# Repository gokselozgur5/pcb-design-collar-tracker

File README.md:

# Collar Tracker

**A GNSS + cellular dog tracker, engineered across hardware, firmware and enclosure.**

A custom six-layer PCB, a persistent position-delivery pipeline and an adjustable collar mount.
Designed for factory assembly, with versioned sources and reproducible verification.

**Stage:** engineering prototype. PCB fabrication checks pass; assembly approval and physical validation remain open.

[Explore the CAD package](release/collar-tracker-3d-universal-mount-r01.zip) · [Current status](docs/STATUS.md) · [Verification](#verification) · [Start here](#inspect-and-reproduce)

## At a glance

| Hardware | Firmware & service | Mechanical design |
| --- | --- | --- |
| **40 × 32 mm**, six copper layers | **C / Zephyr / nRF Connect SDK** | **57.4 × 49.4 × 21 mm** rigid enclosure |
| nRF9151 · GNSS · LTE-M · nano-SIM | Persistent outbox · mTLS · watchdog recovery | Retained PCB and battery · gasketed lid |
| Independent hot/cold charging interlock | MCUboot signed boot · Python/SQLite receiver | Two adjustable straps · flat and round collar pads |

## Hardware and fit

<table>
<tr>
<td width="50%"></td>
<td width="50%"></td>
</tr>
<tr>
<td><b>Current PCB.</b> 81 fitted components, 44 exact part numbers, two dedicated ground planes.</td>
<td><b>Adjustable attachment.</b> Two replaceable wrap straps and interchangeable grip pads; six nominal collar examples checked.</td>
</tr>
</table>

*CAD illustrations: four PCB package bodies are dimensional substitutes; installed bands show routing envelopes. Physical grip, comfort and ingress protection are unqualified.*

[Native KiCad source](experiments/pcba-r05m-rohm-q1/hardware/) · [BOM and placement review](assembly/pcba-r03/README.md) · [Dimensions and mount assembly](mechanical/universal-mount-r01/README.md)

## System architecture

The device persists each valid fix before attempting a network connection.
The receiver commits the record before acknowledging its sequence; only a matching acknowledgment removes the oldest queued record.
Retries are idempotent for the same device, sequence and payload.
The receiver is a local integration target; no public service or production credentials are configured.

[Tracker firmware](firmware/tracker-r03/README.md) · [Recovery behavior](firmware/tracker-r02/README.md) · [Receiver protocol](firmware/receiver/README.md)

## Engineering decisions

- **Preserve failure ownership.** A DNS timeout bounds the caller's wait; the resolver still owns its eventual result. Late results are freed, overlapping calls are prevented, and expired watchdog leases stay expired.
- **Confirm updates with useful work.** A trial image must persist a fresh fix, receive an upload acknowledgment and remain healthy within a bounded window. Signed boot and trial policy are implemented; update delivery and hardware rollback testing remain open.
- **Keep charging protection independent.** Hardware temperature comparators control charge enable independently of application firmware. Powered fault testing is still required.
- **Make releases inspectable.** Native sources, manufacturing outputs, supplier reports and checks are tied together by hashes. Rejected experiments remain available alongside the chosen design.

## Verification

| Layer | Recorded result | Evidence |
| --- | --- | --- |
| Native CAD | Zero DRC/ERC findings, open connections and schematic mismatches under the documented check profile | [Reports and exclusions](assembly/pcba-r03/native-checks.json) |
| PCB fabrication | Two JLC PCB analyses: **0 Danger / 0 Warning** on identical Gerber bytes and unchanged rules | [Report 1](experiments/power-r05l-charge-interlock/evidence/jlc-check1/report.pdf) · [Report 2](experiments/power-r05l-charge-interlock/evidence/jlc-check2/report.pdf) |
| Firmware | Custom-target builds, image/signature inspection and host fault-injection tests | [Build and test evidence](firmware/evidence/tracker-r03/build-evidence.json) |
| Mechanics | **33** closed meshes; **25** nominal interference queries with no positive-volume intersection | [Meshes](mechanical/universal-mount-r01/mesh-checks.json) · [Fit checks](mechanical/universal-mount-r01/fit-checks.json) |

The current **r05m** part-selection revision preserves the tested **r05l** copper and Gerber bytes.
These are saved results; the integrity checker does not rerun KiCad, JLC or physical tests.

**Next gates:** resolve the [SMT/model and process findings](assembly/pcba-r03/smt-disposition.md), then validate assembled hardware, provisioning, radio behavior, battery runtime and the complete enclosure.
Türkiye operator compatibility, physical mount comfort and IP68 remain unqualified; heart-rate sensing is not implemented.

## Inspect and reproduce

```sh
git clone --depth 1 https://github.com/gokselozgur5/pcb-design-collar-tracker.git
cd pcb-design-collar-tracker
python3 scripts/verify_handoff.py
```

The command checks saved evidence and artifact integrity without changing CAD or contacting a manufacturer.
For the interactive model, extract the [CAD package](release/collar-tracker-3d-universal-mount-r01.zip) and open `mechanical/universal-mount-r01/viewer.html` locally.

| Start with | What it contains |
| --- | --- |
| [STATUS](docs/STATUS.md) / [RESUME](docs/RESUME.md) | Exact active revisions, open work and toolchain commands |
| [PCB Design handbook](docs/PCB_DESIGN.md) | Requirements, source review, routing, verification and release workflow |
| [Firmware build guide](firmware/tracker-r03/README.md) | Pinned build inputs, image inspection and test scope |
| [Manufacturing review](assembly/pcba-r03/README.md) | Selected parts, placement data and remaining assembly gates |
| [Work log](docs/WORKLOG.md) / [Media sources](docs/media/README.md) | Design history and reproducible README visuals |

The root `hardware/` directory is historical. Use the active sources linked above.

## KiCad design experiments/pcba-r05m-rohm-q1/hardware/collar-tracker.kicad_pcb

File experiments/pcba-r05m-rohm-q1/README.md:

# r05m Q1 sourcing revision

Native source for the ROHM UM6K34NTCN selection described in
[PCBA r03](../../assembly/pcba-r03/README.md). Q1 replaces DMN62D2UDW-7.
Only its symbol/value/MPN/datasheet strings change. All other copied native
files, copper geometry, pads, nets, stack and rules remain identical to r05l.
The original r05l source is preserved.

Fresh KiCad 10 DRC/ERC/open-net/schematic-parity reports are under `evidence/`.
The inherited five DRC and four ERC disabled categories are unchanged and are
listed in [native-checks.json](../../assembly/pcba-r03/native-checks.json).
Use the existing r05l Gerber; it contains no substituted part strings and is
reused byte for byte. No new PCB DFM pass is claimed.

This is the next prototype candidate, not a manufacturing release. The actual
SMT run has unresolved findings; current continuation is in
[STATUS](../../docs/STATUS.md).

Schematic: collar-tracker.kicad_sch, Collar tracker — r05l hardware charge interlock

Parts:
C1: 1uF /10V; C1_C_0201_0603Metric; MPN GRM033R61A105ME15D
C2: 1uF /10V; C2_C_0201_0603Metric; MPN GRM033R61A105ME15D
C3: 47uF /10V; C3_C_0805_2012Metric; MPN GRM21BR61A476ME15L
C4: 10uF /10V; C4_C_0603_1608Metric; MPN GRM188R61A106MAALD
C5: 100nF; C5_C_0201_0603Metric; MPN GRM033R60J104ME19D
C6: 4.7uF; C6_C_0402_1005Metric; MPN GRM155R60J475ME47D
C7: 4.7uF; C7_C_0402_1005Metric; MPN GRM155R60J475ME47D
C8: 100nF; C8_C_0201_0603Metric; MPN GRM033R60J104ME19D
C9: 1uF /16V X7R; C9_C_0805_2012Metric; MPN GRM21BR71C105KA01L
C10: 100nF; C10_C_0402_1005Metric; MPN GRM155R71C104KA88D
C11: DNP / tune; C11_C_0402_1005Metric; not fitted
C12: DNP / tune; C12_C_0402_1005Metric; not fitted
C13: 39pF RF; C13_C_0402_1005Metric; MPN GJM1555C1H390FB01D
C14: 39pF RF; C14_C_0402_1005Metric; MPN GJM1555C1H390FB01D
C15: 100nF; C15_C_0402_1005Metric; MPN GRM155R71C104KA88D
C16: 1uF; C16_C_0402_1005Metric; MPN GRM155R61A105KE15D
C17: 1uF /10V; C17_C_0402_1005Metric; MPN GRM155R61A105KE15D
C18: 10uF /10V; C18_C_0603_1608Metric; MPN GRM188R61A106MAALD
C19: 1uF /10V; C19_C_0402_1005Metric; MPN GRM155R61A105KE15D
C20: 1uF; C20_C_0402_1005Metric; MPN GRM155R61A105KE15D
C21: 1uF; C21_C_0402_1005Metric; MPN GRM155R61A105KE15D
C23: 100nF; C23_C_0402_1005Metric; MPN GRM155R71C104KA88D
C24: 100nF; C24_C_0402_1005Metric; MPN GRM155R71C104KA88D
C25: 1uF /16V X7R; C25_C_0805_2012Metric; MPN GRM21BR71C105KA01L
C26: 47nF /16V X7R; C26_C_0402_1005Metric; MPN GRM155R71C473KA01D
C27: 100nF /16V X7R; C27_C_0402_1005Metric; MPN GRM155R71C104KA88D
C28: 100nF /16V X7R; C28_C_0402_1005Metric; MPN GRM155R71C104KA88D
C29: 100nF /16V X7R; C29_C_0402_1005Metric; MPN GRM155R71C104KA88D
C30: 100nF /16V X7R; C30_C_0402_1005Metric; MPN GRM155R71C104KA88D
C31, C32, C33: 100nF /16V; C30_C_0402_1005Metric; MPN GRM155R71C104KA88D
C34, C35, C36: 1nF /50V C0G; C30_C_0402_1005Metric; MPN GRM1555C1H102JA01D
D1, D2: TPD4E1U06DCKR; MPN TPD4E1U06DCKR
FB1: 22R @100MHz; FB1_L_0603_1608Metric; MPN BLM18SD220SN1D
J1: LTE antenna / 50R; J1_U.FL_Hirose_U.FL-R-SMT-1_Vertical; MPN U.FL-R-SMT-1(10)
J2: GNSS antenna / passive; J2_U.FL_Hirose_U.FL-R-SMT-1_Vertical; MPN U.FL-R-SMT-1(10)
J3: 5V charging input; J3_Solder_1x02_P2.5mm
J4: Protected cell + NTC; J4_Solder_1x03_P2.5mm
J5: DIGITAL health sensor interface; J5_Contact_2x06_P1.27mm
J6: SIM8051-6-0-14-00-A; SIM8051_6_0_14_00_A; MPN SIM8051-6-0-14-00-A
J7: SWD / debug; J7_Contact_2x03_P1.27mm
L1: 9.1nH; L1_L_0402_1005Metric; MPN LQW15AN9N1J00D
Q1: UM6K34NTCN; Q1_SOT-363_SC-70-6; MPN UM6K34NTCN
R1: 22k /1%; R1_R_0402_1005Metric; MPN RC0402FR-0722KL
R2: 1k; R2_R_0402_1005Metric; MPN RC0402FR-071KL
R3: 0R / tune; R3_R_0402_1005Metric; MPN RC0402JR-070RL
R4: 1k; R4_R_0402_1005Metric; MPN RC0402FR-071KL
R5: 100k; R5_R_0402_1005Metric; MPN RC0402FR-07100KL
R6: 18k /1%; R6_R_0402_1005Metric; MPN RC0402FR-0718KL
R7: 3k /1%; R7_R_0402_1005Metric; MPN RC0402FR-073KL
R8: 10k; R8_R_0402_1005Metric; MPN RC0402FR-0710KL
R9: 10k; R9_R_0402_1005Metric; MPN RC0402FR-0710KL
R12: 4.7k; R12_R_0402_1005Metric; MPN RC0402FR-074K7L
R13: 4.7k; R13_R_0402_1005Metric; MPN RC0402FR-074K7L
R14: 100k; R14_R_0402_1005Metric; MPN RC0402FR-07100KL
R15: 100k; R15_R_0402_1005Metric; MPN RC0402FR-07100KL
R16: 10k /1%; R16_R_0402_1005Metric; MPN RC0402FR-0710KL
R17: 200k /0.1%; R17_R_0402_1005Metric; MPN RT0402BRD07200KL
R18: 26.1k /0.1%; R18_R_0402_1005Metric; MPN RT0402BRD0726K1L
R19: 3.4M /1%; R19_R_0402_1005Metric; MPN RC0402FR-073M4L
R20: 10k /1%; R20_R_0402_1005Metric; MPN RC0402FR-0710KL
R21: 22R /1%; R21_R_0402_1005Metric; MPN CRCW040222R0FKEDHP
R22: 1M /1%; R22_R_0402_1005Metric; MPN RC0402FR-071ML
R23: 100k /1%; R23_R_0402_1005Metric; MPN RC0402FR-07100KL
R24: 196k /0.1%; R16_R_0402_1005Metric; MPN RT0402BRD07196KL
R25, R27: 49.9k /0.1%; R16_R_0402_1005Metric; MPN RT0402BRD0749K9L
R26: 27.4k /0.1%; R16_R_0402_1005Metric; MPN RT0402BRD0727K4L
R28, R29, R30: 100k; R16_R_0402_1005Metric; MPN RC0402FR-07100KL
U1: nRF9151-LACA; U1_LGA_9151_12.1x11.1mm; MPN NRF9151-LACA-R
U2: SKY65943-11; U2_SKY65943_DK10171; MPN SKY65943-11
U3: BQ25185DLHR; U3_Texas_DLH0010A_WSON-10-1EP_2.2x2mm_P0.4mm_EP0.9x1.5mm; MPN BQ25185DLHR
U4: TPS7A0218PDBVR; U4_SOT-23-5; MPN TPS7A0218PDBVR
U5: LIS2DW12TR; U5_LGA-12_2x2mm_P0.5mm; MPN LIS2DW12TR
U6: TPS3808G01DBVR; U6_SOT-23-6; MPN TPS3808G01DBVR
U7: TPS3808G30DBVR; U7_SOT-23-6; MPN TPS3808G30DBVR
U8: SN74LVC1G14DCKR; U8_SOT-353_SC-70-5; MPN SN74LVC1G14DCKR
U9: MAX17048G+T10; U9_MAX17048_T822_3_90_0065E; MPN MAX17048G+T10
U10: TLV3012BIDCKR / HOT; TI_DCK0006A; MPN TLV3012BIDCKR
U11: TLV3012BIDCKR / COLD; TI_DCK0006A; MPN TLV3012BIDCKR
U12: SN74LVC1G00DCKR; TI_DCK0005A; MPN SN74LVC1G00DCKR

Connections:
/ACC_INT: U1.58 (P0.02), U5.12 (INT1)
/AMP_IN: L1.2, U2.8 (AMP_IN)
/BAT_NTC: C36.1, J4.3, U3.6 (TS_MR), U10.3 (IN+), U11.4 (IN-)
/CHARGE_DISABLE: R28.2, U3.4 (nCE), U12.4 (Y_DISABLE)
/CHG_COLD_LIMIT: R26.2, R27.1, U11.3 (IN+)
/CHG_COLD_OK: R30.1, U11.1 (OUT), U12.2 (B_COLD_OK)
/CHG_COLD_REF: C35.1, R26.1, U11.5 (REF_1V242)
/CHG_FAULT: R9.1, U1.70 (P0.11), U3.3 (STAT2)
/CHG_HOT_LIMIT: R24.2, R25.1, U10.4 (IN-)
/CHG_HOT_OK: R29.1, U10.1 (OUT), U12.1 (A_HOT_OK)
/CHG_HOT_REF: C34.1, R24.1, U10.5 (REF_1V242)
/CHG_STAT: R8.1, U1.69 (P0.10), U3.9 (STAT1)
/COEX0: R4.1, U1.52 (COEX0)
/DEBUG_RESET: J7.5, R2.2
/DEC0: C7.1, U1.24 (DEC0)
/FG_ALERT: R23.2, U1.73 (P0.13), U9.5 (ALRT_N)
/FILT_OUT: L1.1, U2.7 (FILT_OUT)
/GND: C1.2, C2.2, C3.2, C4.2, C5.2, C6.2, C7.2, C8.2, C9.2, C10.2, C11.2, C12.2, C15.2, C16.2, C17.2, C18.2, C19.2, C20.2, C21.2, C23.2, C24.2, C25.2, C26.2, C27.2, C28.2, C29.2, C30.2, C31.2, C32.2, C33.2, C34.2, C35.2, C36.2, D1.2 (GND), D2.2 (GND), J1.2, J2.2, J3.2, J4.2, J5.1, J6.5 (GND), J6.8 (GND), J7.3, Q1.1 (S1), Q1.4 (S2), R5.2, R6.2, R7.2, R15.2, R18.2, R22.2, R25.2, R27.2, R29.2, R30.2, U1.1 (GND), U1.7 (GND), U1.13 (GND), U1.15 (GND), U1.20 (GND), U1.25 (GND), U1.30 (GND), U1.34 (GND), U1.36 (GND), U1.38 (GND), U1.39 (GND), U1.40 (GND), U1.41 (GND), U1.43 (GND), U1.46 (GND), U1.51 (GND), U1.55 (GND), U1.60 (GND), U1.66 (GND), U1.71 (GND), U1.76 (GND), U1.105 (GND), U1.106 (GND), U1.107 (GND), U1.108 (GND), U1.109 (GND), U1.110 (GND), U1.111 (GND), U1.112 (GND), U1.113 (GND), U2.1 (GND), U2.4 (GND), U2.6 (GND), U2.9 (GND), U2.11 (GND), U3.5 (GND), U3.11 (GND), U4.2 (GND), U5.6 (GND), U5.7 (GND), U5.8 (GND), U6.2 (GND), U7.2 (GND), U8.3 (GND), U9.1 (GND), U9.4 (GND), U9.6 (QSTRT), U9.9 (GND), U10.2 (GND), U11.2 (GND), U12.3 (GND)
/GNSS_ANT: C14.1, J2.1
/GNSS_FEM_IN: C14.2, U2.5 (RF_IN)
/GNSS_FEM_OUT: C13.1, U2.10 (RF_OUT)
/GNSS_LNA_EN: R4.2, R5.1, U2.2 (VEN)
/GPS_RF: C13.2, U1.42 (GPS)
/HEALTH_CS: J5.10, R14.1, U1.64 (P0.07)
/HEALTH_EN: J5.12, R15.1, U1.68 (P0.09)
/HEALTH_INT: J5.6, U1.59 (P0.03)
/HEALTH_RESET: J5.11, U1.67 (P0.08)
/I2C_SCL: J5.5, R13.1, U1.57 (P0.01), U5.1 (SCL), U9.7 (SCL)
/I2C_SDA: J5.4, R12.1, U1.56 (P0.00), U5.4 (SDA), U9.8 (SDA)
/ILIM_VSET: R6.1, U3.7 (ILIM_VSET)
/ISET: R7.1, U3.8 (ISET)
/LTE_ANT: C12.1, J1.1, R3.2
/LTE_RF: C11.1, R3.1, U1.35 (ANT)
/NRF_ENABLE: C9.1, R1.2, U1.10 (ENABLE), U7.5 (SENSE)
/NRF_RESET: C8.1, R2.1, U1.9 (nRESET_2V2)
/POWER_FAULT: Q1.2 (G1), Q1.5 (G2), R22.1, U8.4 (Y)
/POWER_GOOD: R1.1, R16.2, R19.1, U6.1 (RESET_N), U7.3 (MR_N), U8.2 (A)
/SIM_1V8: C10.1, D1.6 (D1-), J6.1 (C1_VCC), U1.19 (SIM_1V8)
/SIM_CLK: D1.3 (D2+), J6.3 (C3_CLK), U1.18 (SIM_CLK)
/SIM_IO: D2.3 (D2+), J6.7 (C7_IO), U1.17 (SIM_IO)
/SIM_RST: D1.1 (D1+), J6.2 (C2_RST), U1.16 (SIM_RST)
/SPI_MISO: J5.9, U1.63 (P0.06)
/SPI_MOSI: J5.8, U1.62 (P0.05)
/SPI_SCK: J5.7, U1.61 (P0.04)
/SWDCLK: J7.4, U1.3 (SWDCLK)
/SWDIO: J7.2, U1.4 (SWDIO)
/UV_DELAY: C25.1, U6.4 (CT)
/UV_SENSE: R17.2, R18.1, R19.2, U6.5 (SENSE)
/VBAT: C19.1, C30.1, J4.1, U3.2 (BAT), U9.2 (CELL_NC_CONNECT_BAT), U9.3 (VDD)
/VDD_NRF: C3.1, C4.1, C27.1, C28.1, C29.1, FB1.2, R16.1, R17.1, R20.1, U1.14 (VDD), U6.3 (MR_N), U6.6 (VDD), U7.6 (VDD), U8.5 (VCC)
/VIN_5V: C17.1, J3.1, U3.10 (IN)
/VIO_1V8: C5.1, C6.1, C15.1, C16.1, C21.1, C23.1, C24.1, J5.2, J7.1, R8.2, R9.2, R12.2, R13.2, R14.2, R21.1, R23.1, U1.65 (VDD_GPIO), U2.3 (VCC), U4.5 (OUT_1V8), U5.2 (CS), U5.3 (SA0), U5.9 (VDD), U5.10 (VDD_IO)
/VIO_DELAY: C26.1, U7.4 (CT)
/VIO_DISCHARGE: Q1.6 (D1), R21.2
/VIO_ENABLE: Q1.3 (D2), R20.2, U4.3 (EN), U7.1 (RESET_N)
/VSYS: C1.1, C2.1, C18.1, C20.1, C31.1, C32.1, C33.1, FB1.1, J5.3, J7.6, R28.1, U3.1 (SYS), U4.1 (IN), U10.6 (V+), U11.6 (V+), U12.5 (VCC)

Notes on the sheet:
r05k SELECTED COMPONENTS — PHYSICAL ELECTRICAL / RF QUALIFICATION OPEN
Circuit topology retains r05; PCB routing retains r05j. R17/R18/R19: 200k / 26.1k / 3.4M; C25: 1uF. All 65 fitted component references have exact candidate MPNs.
Power control: U6 supervises the modem rail; R19 adds hysteresis. U7 delays the 1.8 V rail after NRF_ENABLE rises. U8/Q1 disable U4 and discharge VIO on POWER_GOOD low. U9 reads the protected cell over the switched-domain I2C bus.
HOLD: validate threshold/timing corners, effective capacitance, brief faults, supply collapse, low-cell charging recovery and off-state interfaces. No powered validation or order approval.
Protected pack/NTC and actual LTE/GNSS antennas remain unselected. Firmware must wait for VIO, recover I2C and configure the fuel gauge. Do not quick-start the gauge on every processor reset.
09 / HARDWARE CELL-TEMPERATURE CHARGE INTERLOCK
Both comparator outputs must be HIGH to enable charging. POR outputs LOW; NAND drives /CE HIGH. Always-on VSYS supply: independent of MCU/VIO reset and undervoltage shutdown. Candidate 103JT-025 must be bonded to the cell. Open/short sensor inhibits charging. Conservative window; threshold toleranc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

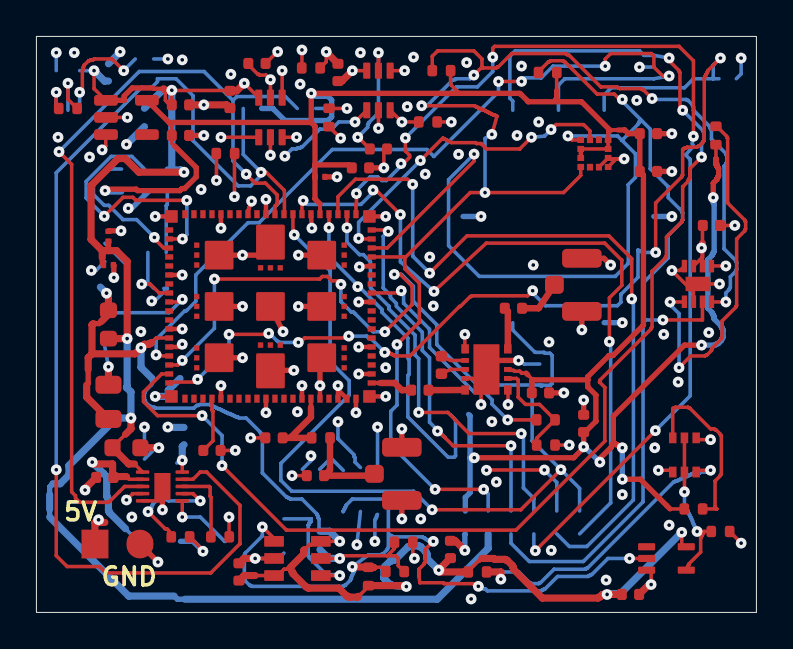
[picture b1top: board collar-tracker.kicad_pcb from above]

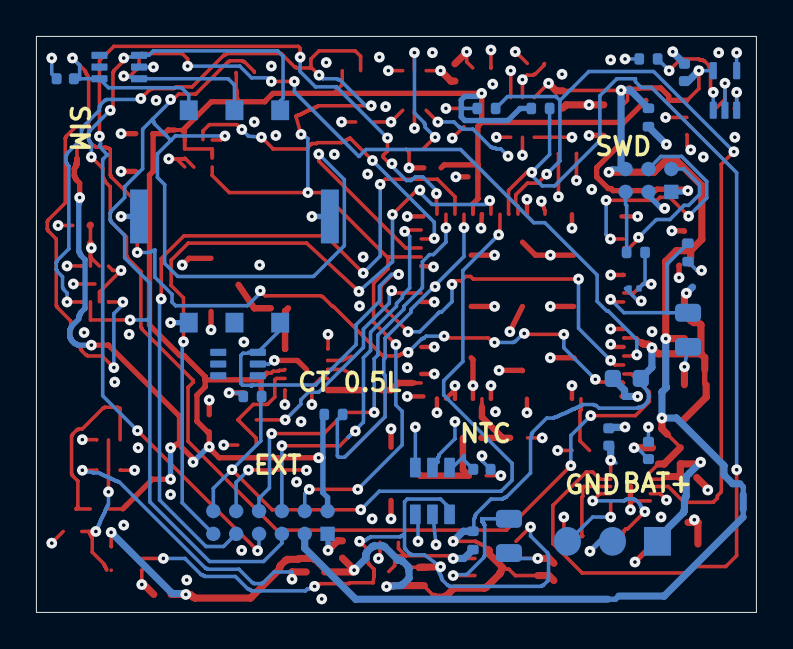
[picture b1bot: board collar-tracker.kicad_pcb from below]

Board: 6 copper layers, 40.0 x 32.0 mm, 87 parts (26 on the bottom side), 56 nets.

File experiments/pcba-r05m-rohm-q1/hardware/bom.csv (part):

ref,value,mpn,footprint,dnp,onboard,status
U1,nRF9151-LACA,NRF9151-LACA-R,Collar033:U1_LGA_9151_12.1x11.1mm,False,True,"Exact prototype candidate MPN; electrical, RF and assembly acceptance remain open"
FB1,22R @100MHz,BLM18SD220SN1D,Collar033:FB1_L_0603_1608Metric,False,True,"Exact prototype candidate MPN; electrical, RF and assembly acceptance remain open"
C1,1uF /10V,GRM033R61A105ME15D,Collar033:C1_C_0201_0603Metric,False,True,"Exact prototype candidate MPN; electrical, RF and assembly acceptance remain open"
C2,1uF /10V,GRM033R61A105ME15D,Collar033:C2_C_0201_0603Metric,False,True,"Exact prototype candidate MPN; electrical, RF and assembly acceptance remain open"
C3,47uF /10V,GRM21BR61A476ME15L,Collar033:C3_C_0805_2012Metric,False,True,"Exact prototype candidate MPN; electrical, RF and assembly acceptance remain open"
C4,10uF /10V,GRM188R61A106MAALD,Collar033:C4_C_0603_1608Metric,False,True,"Exact prototype candidate MPN; electrical, RF and assembly acceptance remain open"
C5,100nF,GRM033R60J104ME19D,Collar033:C5_C_0201_0603Metric,False,True,"Exact prototype candidate MPN; electrical, RF and assembly acceptance remain open"
C6,4.7uF,GRM155R60J475ME47D,Collar033:C6_C_0402_1005Metric,False,True,"Exact prototype candidate MPN; electrical, RF and assembly acceptance remain open"
C7,4.7uF,GRM155R60J475ME47D,Collar033:C7_C_0402_1005Metric,False,True,"Exact prototype candidate MPN; electrical, RF and assembly acceptance remain open"
C8,100nF,GRM033R60J104ME19D,Collar033:C8_C_0201_0603Metric,False,True,"Exact prototype candidate MPN; electrical, RF and assembly acceptance remain open"
R1,22k /1%,RC0402FR-0722KL,Collar033:R1_R_0402_1005Metric,False,True,"Exact prototype candidate MPN; electrical, RF and assembly acceptance remain open"
C9,1uF /16V X7R,GRM21BR71C105KA01L,Collar05:C9_C_0805_2012Metric,False,True,"Exact prototype candidate MPN; electrical, RF and assembly acceptance remain open"
R2,1k,RC0402FR-071KL,Collar033:R2_R_0402_1005Metric,False,True,"Exact prototype candidate MPN; electrical, RF and assembly acceptance remain open"
C10,100nF,GRM155R71C104KA88D,Collar033:C10_C_0402_1005Metric,False,True,"Exact prototype candidate MPN; electrical, RF and assembly acceptance remain open"
R3,0R / tune,RC0402JR-070RL,Collar033:R3_R_0402_1005Metric,False,True,"Exact prototype candidate MPN; electrical, RF and assembly acceptance remain open"
C11,DNP / tune,,Collar033:C11_C_0402_1005Metric,True,True,candidate
C12,DNP / tune,,Collar033:C12_C_0402_1005Metric,True,True,candidate
J1,LTE antenna / 50R,U.FL-R-SMT-1(10),Collar033:J1_U.FL_Hirose_U.FL-R-SMT-1_Vertical,False,True,"Exact prototype candidate MPN; electrical, RF and assembly acceptance remain open"
U2,SKY65943-11,SKY65943-11,Collar033:U2_SKY65943_DK10171,False,True,"Exact prototype candidate MPN; electrical, RF and assembly acceptance remain open"
L1,9.1nH,LQW15AN9N1J00D,Collar033:L1_L_0402_1005Metric,False,True,"Exact prototype candidate MPN; electrical, RF and assembly acceptance remain open"
C13,39pF RF,GJM1555C1H390FB01D,Collar033:C13_C_0402_1005Metric,False,True,"Exact prototype candidate MPN; electrical, RF and assembly acceptance remain open"
C14,39pF RF,GJM1555C1H390FB01D,Collar033:C14_C_0402_1005Metric,False,True,"Exact prototype candidate MPN; electrical, RF and assembly acceptance remain open"
J2,GNSS antenna / passive,U.FL-R-SMT-1(10),Collar033:J2_U.FL_Hirose_U.FL-R-SMT-1_Vertical,False,True,"Exact prototype candidate MPN; electrical, RF and assembly acceptance remain open"
R4,1k,RC0402FR-071KL,Collar033:R4_R_0402_1005Metric,False,True,"Exact prototype candidate MPN; electrical, RF and assembly acceptance remain open"
R5,100k,RC0402FR-07100KL,Collar033:R5_R_0402_1005Metric,False,True,"Exact prototype candidate MPN; electrical, RF and assembly acceptance remain open"
C15,100nF,GRM155R71C104KA88D,Collar033:C15_C_0402_1005Metric,False,True,"Exact prototype candidate MPN; electrical, RF and assembly acceptance remain open"
C16,1uF,GRM155R61A105KE15D,Collar033:C16_C_0402_1005Metric,False,True,"Exact prototype candidate MPN; electrical, RF and assembly acceptance remain open"
J3,5V charging input,,Collar033:J3_Solder_1x02_P2.5mm,False,True,onboard contact pads; external device/fixture not selected
U3,BQ25185DLHR,BQ25185DLHR,Collar033:U3_Texas_DLH0010A_WSON-10-1EP_2.2x2mm_P0.4mm_EP0.9x1.5mm,False,True,"Exact prototype candidate MPN; electrical, RF and assembly acceptance remain open"
J4,Protected cell + NTC,,Collar033:J4_Solder_1x03_P2.5mm,False,True,onboard contact pads; external device/fixture not selected
C17,1uF /10V,GRM155R61A105KE15D,Collar033:C17_C_0402_1005Metric,False,True,"Exact prototype candidate MPN; electrical, RF and assembly acceptance remain open"
C18,10uF /10V,GRM188R61A106MAALD,Collar033:C18_C_0603_1608Metric,False,True,"Exact prototype candidate MPN; electrical, RF and assembly acceptance remain open"
C19,1uF /10V,GRM155R61A105KE15D,Collar033:C19_C_0402_1005Metric,False,True,"Exact prototype candidate MPN; electrical, RF and assembly acceptance remain open"
R6,18k /1%,RC0402FR-0718KL,Collar033:R6_R_0402_1005Metric,False,True,"Exact prototype candidate MPN; electrical, RF and assembly acceptance remain open"
R7,3k /1%,RC0402FR-073KL,Collar033:R7_R_0402_1005Metric,False,True,"Exact prototype candidate MPN; electrical, RF and assembly acceptance remain open"
R8,10k,RC0402FR-0710KL,Collar033:R8_R_0402_1005Metric,False,True,"Exact prototype candidate MPN; electrical, RF and assembly acceptance remain open"
R9,10k,RC0402FR-0710KL,Collar033:R9_R_0402_1005Metric,False,True,"Exact prototype candidate MPN; electrical, RF and assembly acceptance remain open"
U4,TPS7A0218PDBVR,TPS7A0218PDBVR,Collar033:U4_SOT-23-5,False,True,"Exact prototype candidate MPN; electrical, RF and assembly acceptance remain open"
C20,1uF,GRM155R61A105KE15D,Collar033:C20_C_0402_1005Metric,False,True,"Exact prototype candidate MPN; electrical, RF and assembly acceptance remain open"
C21,1uF,GRM155R61A105KE15D,Collar033:C21_C_0402_1005Metric,False,True,"Exact prototype candidate MPN; electrical, RF and assembly acceptance remain open"
U5,LIS2DW12TR,LIS2DW12TR,Collar033:U5_LGA-12_2x2mm_P0.5mm,False,True,"Exact prototype candidate MPN; electrical, RF and assembly acceptance remain open"
C23,100nF,GRM155R71C104KA88D,Collar033:C23_C_0402_1005Metric,False,True,"Exact prototype candidate MPN; electrical, RF and assembly acceptance remain open"
C24,100nF,GRM155R71C104KA88D,Collar033:C24_C_0402_1005Metric,False,True,"Exact prototype candidate MPN; electrical, RF and assembly acceptance remain open"
R12,4.7k,RC0402FR-074K7L,Collar033:R12_R_0402_1005Metric,False,True,"Exact prototype candidate MPN; electrical, RF and assembly acceptance remain open"
R13,4.7k,RC0402FR-074K7L,Collar033:R13_R_0402_1005Metric,False,True,"Exact prototype candidate MPN; electrical, RF and assembly acceptance remain open"
J5,DIGITAL health sensor interface,,Collar033:J5_Contact_2x06_P1.27mm,False,True,onboard contact pads; external device/fixture not selected
R14,100k,RC0402FR-07100KL,Collar033:R14_R_0402_1005Metric,False,True,"Exact prototype candidate MPN; electrical, RF and assembly acceptance remain open"
R15,100k,RC0402FR-07100KL,Collar033:R15_R_0402_1005Metric,False,True,"Exact prototype candidate MPN; electrical, RF and assembly acceptance remain open"
J6,SIM8051-6-0-14-00-A,SIM8051-6-0-14-00-A,Collar04:SIM8051_6_0_14_00_A,False,True,"Exact prototype candidate MPN; electrical, RF and assembly acceptance remain open"
J7,SWD / debug,,Collar033:J7_Contact_2x03_P1.27mm,False,True,onboard contact pads; external device/fixture not selected
D1,TPD4E1U06DCKR,TPD4E1U06DCKR,Collar04:TPD4E1U06DCKR,False,True,"Exact prototype candidate MPN; electrical, RF and assembly acceptance remain open"
D2,TPD4E1U06DCKR,TPD4E1U06DCKR,Collar04:TPD4E1U06DCKR,False,True,"Exact prototype candidate MPN; electrical, RF and assembly acceptance remain open"
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
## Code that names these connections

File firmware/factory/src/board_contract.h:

#ifndef COLLAR_BOARD_CONTRACT_H
#define COLLAR_BOARD_CONTRACT_H

#include <zephyr/devicetree.h>
#include <zephyr/dt-bindings/gpio/gpio.h>
#include <zephyr/dt-bindings/pinctrl/nrf-pinctrl.h>
#include <zephyr/sys/util.h>

/* Pin numbers are checked against the native r05l schematic before each build. */
#define COLLAR_IO DT_NODELABEL(board_io)
BUILD_ASSERT(DT_GPIO_PIN(COLLAR_IO, charge_status_gpios) == 10, "CHG_STAT pin mismatch");
BUILD_ASSERT(DT_GPIO_PIN(COLLAR_IO, charge_fault_gpios) == 11, "CHG_FAULT pin mismatch");
BUILD_ASSERT(DT_GPIO_PIN(COLLAR_IO, fuel_alert_gpios) == 13, "FG_ALERT pin mismatch");
BUILD_ASSERT(DT_GPIO_PIN(COLLAR_IO, health_enable_gpios) == 9, "HEALTH_EN pin mismatch");
BUILD_ASSERT(DT_GPIO_FLAGS(COLLAR_IO, charge_status_gpios) == GPIO_ACTIVE_LOW,
	     "CHG_STAT polarity mismatch");
BUILD_ASSERT(DT_GPIO_FLAGS(COLLAR_IO, charge_fault_gpios) == GPIO_ACTIVE_LOW,
	     "CHG_FAULT polarity mismatch");
BUILD_ASSERT(DT_GPIO_FLAGS(COLLAR_IO, fuel_alert_gpios) == GPIO_ACTIVE_LOW,
	     "FG_ALERT polarity mismatch");
BUILD_ASSERT(DT_GPIO_FLAGS(COLLAR_IO, health_enable_gpios) == GPIO_ACTIVE_HIGH,
	     "HEALTH_EN polarity mismatch");
BUILD_ASSERT(DT_REG_ADDR(DT_NODELABEL(accelerometer)) == 0x19, "LIS2DW12 SA0 mismatch");
BUILD_ASSERT(DT_REG_ADDR(DT_NODELABEL(battery_gauge)) == 0x36, "MAX17048 address mismatch");
BUILD_ASSERT(DT_PROP(DT_NODELABEL(i2c2), zephyr_deferred_init), "I2C must wait for VIO");
BUILD_ASSERT(DT_PROP(DT_NODELABEL(accelerometer), zephyr_deferred_init),
	     "Accelerometer must wait for VIO");
BUILD_ASSERT(DT_PROP_BY_IDX(DT_CHILD(DT_NODELABEL(board_i2c_default), group1), psels, 0)
	     == NRF_PSEL(TWIM_SDA, 0, 0), "I2C SDA pin mismatch");
BUILD_ASSERT(DT_PROP_BY_IDX(DT_CHILD(DT_NODELABEL(board_i2c_default), group1), psels, 1)
	     == NRF_PSEL(TWIM_SCL, 0, 1), "I2C SCL pin mismatch");

#endif

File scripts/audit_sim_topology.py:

"""Measure SIM paths and check that connector copper reaches the ESD land first."""

import hashlib
import heapq
import itertools
import json
import math
import sys
from pathlib import Path

from shapely.geometry import LineString, Point, Polygon
from shapely.ops import unary_union
from shapely.strtree import STRtree

sys.path.insert(0, str(Path(__file__).resolve().parent))
from audit_power_paths import make_graph


def shortest(graph, start, end):
    serial = itertools.count()
    queue = [(0, next(serial), start)]
    distances = {start: 0}
    previous = {}
    while queue:
        cost, _, node = heapq.heappop(queue)
        if cost != distances[node]:
            continue
        if node == end:
            steps = []
            while node != start:
                node, edge = previous[node]
                if edge["kind"] != "ideal_copper_junction":
                    steps.append(edge)
            return dict(
                length_mm=cost,
                vias=sum(s["kind"] == "via" for s in steps),
                track_ids=list(
                    dict.fromkeys(
                        s["id"] for s in reversed(steps) if s["kind"] == "track"
                    )
                ),
            )
        for other, _, metadata in graph[node]:
            new = cost + metadata.get("length_mm", 0)
            if new < distances.get(other, math.inf):
                distances[other] = new
                previous[other] = (node, metadata)
                heapq.heappush(queue, (new, next(serial), other))
    raise RuntimeError("Disconnected SIM path")


def bypasses_esd_land(geometry, esd, start, end):
    """Cut actual ESD land copper out of this net, then test physical continuity.

    Each remaining polygon is a separate object. Vias join every spanned layer.
    This tests layout topology, not ESD current or IEC immunity.
    """
    cut = unary_union([Polygon(p) for p in esd["poly"]]).buffer(0.001)
    items = []
    for kind, rows in [
        ("pad", geometry["pads"]),
        ("track", geometry["tracks"]),
        ("via", geometry["vias"]),
    ]:
        for item in rows:
            if item["net"] != esd["net"]:
                continue
            layers = item.get("layers", [item.get("layer")])
            shape = (
                unary_union([Polygon(p) for p in item["poly"]])
                if kind == "pad"
                else LineString([item["start"], item["end"]]).buffer(
                    item["width"] / 2, quad_segs=32
                )
                if kind == "track"
                else Point(item["pos"]).buffer(item["diameter"] / 2, quad_segs=96)
            )
            if kind == "via" and shape.intersects(cut):
                raise ValueError(
                    "ESD land overlaps a via; inspect this topology separately"
                )
            shape = shape.difference(cut) if set(layers) & set(esd["layers"]) else shape
            if shape.is_empty:
                continue
            for part in getattr(shape, "geoms", [shape]):
                if part.area:
                    items.append(dict(id=item["id"], shape=part, layers=layers))
    parents = list(range(len(items)))

    def root(i):
        while parents[i] != i:
            parents[i] = parents[parents[i]]
            i = parents[i]
        return i

    for layer in sorted({layer for item in items for layer in item['layers']}):
        ids = [i for i, item in enumerate(items) if layer in item["layers"]]
        shapes = [items[i]["shape"] for i in ids]
        tree = STRtree(shapes)
        for a, i in enumerate(ids):
            for j in tree.query(shapes[a].buffer(0.000002)):
                if shapes[a].distance(shapes[j]) <= 0.000002:
                    parents[root(ids[j])] = root(i)
    first = {root(i) for i, x in enumerate(items) if x["id"] == start["id"]}
    last = {root(i) for i, x in enumerate(items) if x["id"] == end["id"]}
    assert first and last
    return bool(first & last)


def main():
    r = Path(sys.argv[1])
    g = json.loads((r / "evidence/route-geometry.json").read_text())
    assert (
        g["source_sha256"]
        == hashlib.sha256(
            (r / "hardware/collar-tracker.kicad_pcb").read_bytes()
        ).hexdigest()
    )
    pads = {(p["ref"], p["pin"]): p for p in g["pads"]}

    mapping = [("SIM_1V8", "1"), ("SIM_RST", "2"), ("SIM_CLK", "3"), ("SIM_IO", "7")]
    rows = []
    for net, connector_pin in mapping:
        net = "/" + net
        clamps = [p for p in g["pads"] if p["net"] == net and p["ref"] in ["D1", "D2"]]
        assert len(clamps) == 1, "Expected exactly one SIM clamp land"
        esd_ref, esd_pin = clamps[0]["ref"], clamps[0]["pin"]
        graph, terminals = make_graph(g, net, 35, 20, 0.8)
        modem = [p for p in g["pads"] if p["net"] == net and p["ref"] == "U1"]
        assert len(modem) == 1
        m = modem[0]
        start, clamp, end = ("J6", connector_pin), (esd_ref, esd_pin), ("U1", m["pin"])
        rows.append(
            dict(
                net=net,
                connector=".".join(start),
                esd=".".join(clamp),
                modem=".".join(end),
                connector_to_esd=shortest(graph, terminals[start], terminals[clamp]),
                esd_to_modem=shortest(graph, terminals[clamp], terminals[end]),
                connector_to_modem=shortest(graph, terminals[start], terminals[end]),
                bypasses_esd_land=bypasses_esd_land(
                    g, pads[clamp], pads[start], pads[end]
                ),
            )
        )
    report = dict(
        source_sha256=g["source_sha256"],
        paths=rows,
        scope="Track centerline lengths exclude ideal pad/junction spreading. ESD-land cut is a copper-topology check, not a powered ESD test. No plane shortcut is used.",
    )
    (r / "evidence/esd-paths.json").write_text(json.dumps(report, indent=2) + "\n")
    for row in rows:
        print(
            row["net"],
            "entry",
            row["connector_to_esd"]["length_mm"],
            "mm",
            row["connector_to_esd"]["vias"],
            "vias; bypass",
            row["bypasses_esd_land"],
        )


if __name__ == "__main__":
    main()
